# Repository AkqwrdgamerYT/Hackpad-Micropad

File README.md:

##This is my hack pad GitHub repository for my HackPad
A 7 button and 1 potentiometer macropad for opening apps and media controls. 
Potentiometer dial (volume) 
Potentiometer button (mute and unmute) 
Button's 1, 2, and 3 (open YouTube, discord, and opera) 
Button's 4, 5, and 6 (media controls)

demo: https://youtu.be/VbRYApld8Oc
assembly video: not ready yet

#https://github.com/AkqwrdgamerYT/Hackpad-Micropad/blob/main/BOM(Sheet1).csv
For BOM
#https://github.com/AkqwrdgamerYT/Hackpad-Micropad/tree/main/kicad%20stuff%20(PCB%26SCHEM)
For PCB&SCHEM
#https://github.com/AkqwrdgamerYT/Hackpad-Micropad/blob/main/step%20files/all%20files/allfiles.zip
For All STEP Files
#https://github.com/AkqwrdgamerYT/Hackpad-Micropad/blob/main/step%20files
For Step files

BTW I don't have the parts so I can't get instructions on how to assemble it and flash the firmware but when I get it I will make a yt video on how to assemble it and it will be linked under demo when ready

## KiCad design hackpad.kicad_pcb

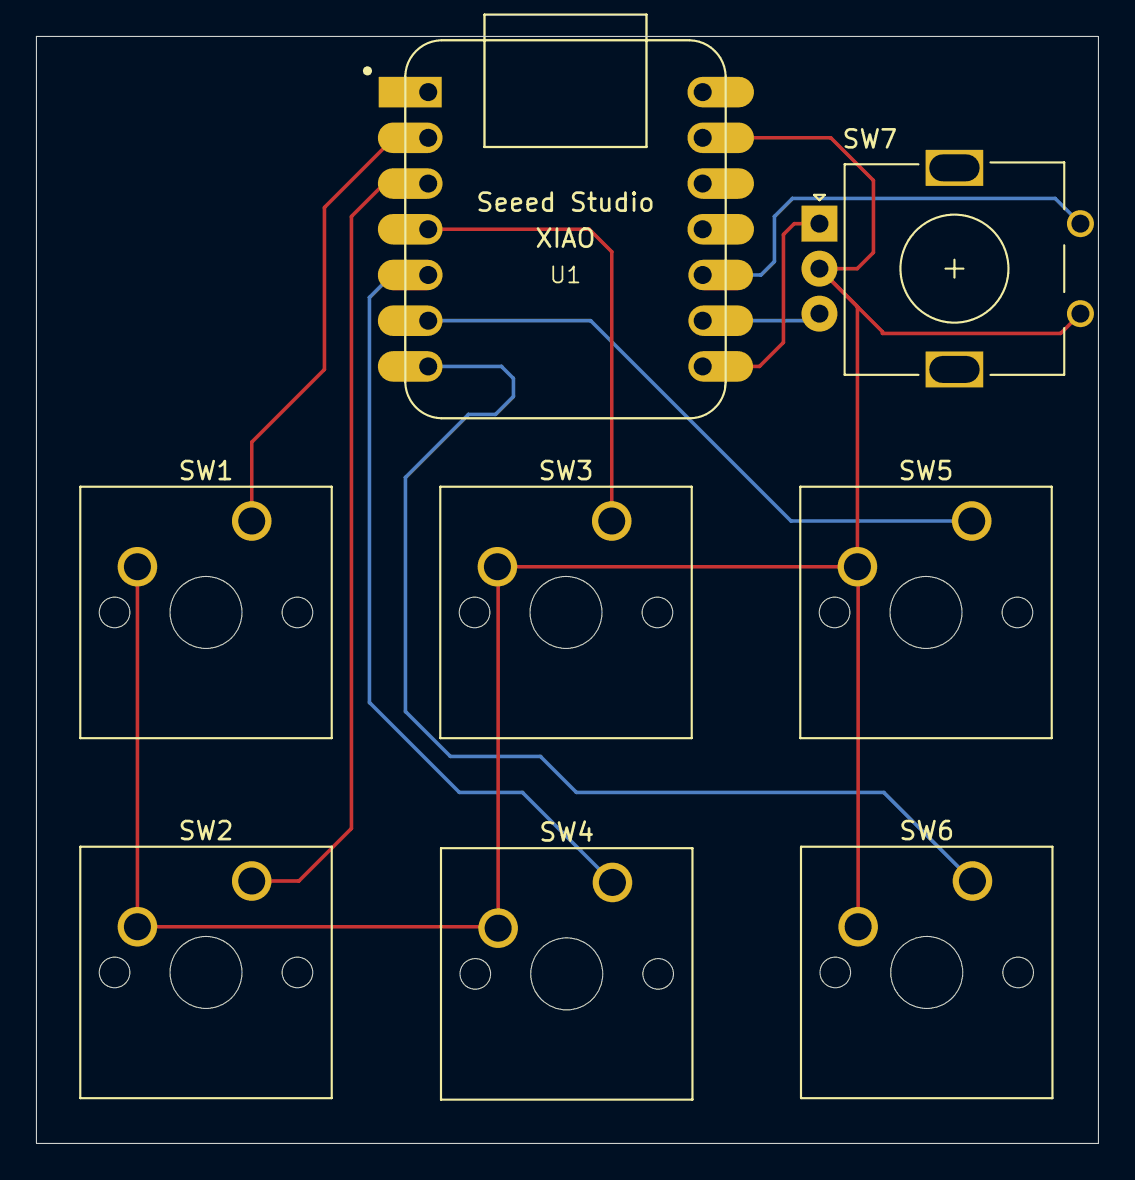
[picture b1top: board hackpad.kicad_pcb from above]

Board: 2 copper layers, 59.0 x 61.5 mm, 8 parts (0 on the bottom side), 9 nets.

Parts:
SW1, SW2, SW3, SW4, SW5, SW6: SW_Push; SW_Cherry_MX_1.00u_PCB
SW7: RotaryEncoder_Switch; RotaryEncoder_Alps_EC11E_Vertical_H20mm
U1: MOUDLE-SEEEDUINO-XIAO; XIAO-Generic-Hybrid-14P-2.54-21X17.8MM

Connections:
GND: SW1.2, SW2.2, SW3.2, SW4.2, SW5.2, SW6.2, SW7.C, U1.13 (GND)
unnamed: SW1.1, U1.2 (PA4_A1_D1)
unnamed: SW7.B, U1.9 (PA7_A8_D8_SCK)
unnamed: SW4.1, U1.5 (PA8_A4_D4_SDA)
unnamed: SW5.1, U1.6 (PA9_A5_D5_SCL)
unnamed: SW2.1, U1.3 (PA10_A2_D2)
unnamed: SW3.1, U1.4 (PA11_A3_D3)
unnamed: SW6.1, U1.7 (PB08_A6_D6_TX)
unnamed: SW7.A, U1.8 (PB09_A7_D7_RX)

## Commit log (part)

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2026-06-11 Add README.md file to repository
2026-06-11 Rename Screenshot 2026-06-11 101928.png to pcb sachem
